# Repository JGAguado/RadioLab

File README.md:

[![GitHub Release][releases-shield]][releases]
[![License][license-shield]](LICENSE)

[![Project Maintenance][maintenance-shield]][maintenance]
[![BuyMeCoffee][buymecoffee-shield]][buymecoffee]

# RadioLab
The RadioLab board is an electronic board intended for transmitting wireless signal values in the most easy and transparent way for the user.

## Project tree

<li><a href="./Design/">Design</a></li>
<li><a href="./Documentation/">Documentation</a></li>

<li><a href="./README.md">README.md</a></li>

[releases-shield]: https://img.shields.io/github/release/JGAguado/RadioLab.svg?style=for-the-badge
[releases]: https://github.com/JGAguado/RadioLab/releases

[license-shield]: https://img.shields.io/badge/License-CC%20BY--NC--SA%204.0-lightgrey.svg?style=for-the-badge

[maintenance-shield]: https://img.shields.io/badge/maintainer-J.%20G.%20Aguado-blue.svg?style=for-the-badge
[maintenance]: https://github.com/JGAguado

[buymecoffee-shield]: https://img.shields.io/badge/buy%20me%20a%20coffee-support-yellow.svg?style=for-the-badge
[buymecoffee]: https://www.buymeacoffee.com/J.G.Aguado

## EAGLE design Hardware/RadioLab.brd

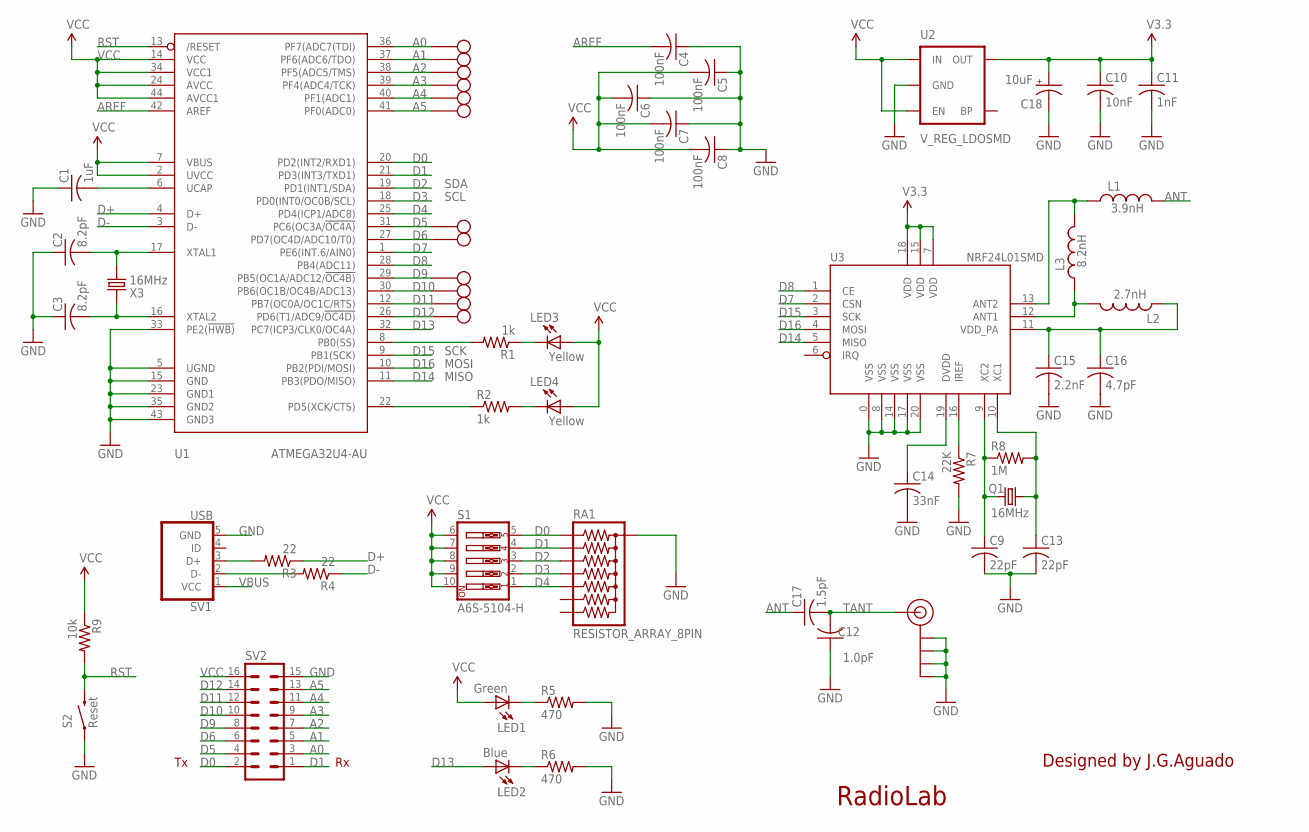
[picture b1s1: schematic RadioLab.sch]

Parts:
ANT: SMA_EDGE; SMA-EDGE
C1: 1uF; C0402
C2, C3: 8.2pF; C0402
C4, C5, C6, C7, C8: 100nF; C0402
C9, C13: 22pF; C0402
C10: 10nF; C0402
C11: 1nF; C0402
C12: 1.0pF; C0402
C14: 33nF; C0402
C15: 2.2nF; C0402
C16: 4.7pF; C0402
C17: 1.5pF; C0402
C18: 10uF; EIA3216
L1: 3.9nH; C0402
L2: 2.7nH; C0402
L3: 8.2nH; C0402
LED1: Green; SML0603
LED2: Blue; SML0603
LED3, LED4: Yellow; SML0603
Q1: 16MHz; CRYSTAL-SMD-5X3
R1, R2: 1k; R0402
R3, R4: 22; R0402
R5, R6: 470; R0402
R7: 22K; R0402
R8: 1M; R0402
R9: 10k; R0402
RA1: RESISTOR_ARRAY_8PIN; CRA12E
S1: A6S-5104-H
S2: Reset; TACTILE_SWITCH_TALL
SV1: USB; FCI-10103594-0001LF
SV2: MA08-2
U1: ATMEGA32U4-AU; TQFP44
U2: V_REG_LDOSMD; SOT23-5
U3: NRF24L01SMD; QFN20
U$1, U$2, U$3, U$4, U$5, U$6, U$7, U$8, U$9, U$10, U$11, U$12: PIN_PAD_CIRCLE_R50; PAD_5MM
X3: 16MHz; 2P-SMD-5X3.2

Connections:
3.3V: C10.1, C11.1, C18.A (+), U2.5 (OUT), U3.7 (VDD), U3.15 (VDD), U3.18 (VDD)
A0: SV2.3, U1.36 (PF7(ADC7(TDI)), U$1.PAD
A1: SV2.5, U1.37 (PF6(ADC6/TDO)), U$2.PAD
A2: SV2.7, U1.38 (PF5(ADC5/TMS)), U$3.PAD
A3: SV2.9, U1.39 (PF4(ADC4/TCK)), U$4.PAD
A4: SV2.11, U1.40 (PF1(ADC1)), U$5.PAD
A5: SV2.13, U1.41 (PF0(ADC0)), U$6.PAD
ANT: C17.1, L1.2
AREF: C4.2, U1.42 (AREF)
D0: RA1.1, S1.5, SV2.2, U1.20 (PD2(INT2/RXD1))
D1: RA1.2, S1.4, SV2.1, U1.21 (PD3(INT3/TXD1))
D2: RA1.3, S1.3, U1.19 (PD1(INT1/SDA))
D3: RA1.4, S1.2, U1.18 (PD0(INT0/OC0B/SCL))
D4: RA1.5, S1.1, U1.25 (PD4(ICP1/ADC8))
D5: SV2.4, U1.31 (PC6(OC3A/!OC4A)), U$7.PAD
D6: SV2.6, U1.27 (PD7(OC4D/ADC10/T0)), U$8.PAD
D7: U1.1 (PE6(INT.6/AIN0)), U3.2 (CSN)
D8: U1.28 (PB4(ADC11)), U3.1 (CE)
D9: SV2.8, U1.29 (PB5(OC1A/ADC12/!OC4B)), U$9.PAD
D10: SV2.10, U1.30 (PB6(OC1B/OC4B/ADC13)), U$10.PAD
D11: SV2.12, U1.12 (PB7(OC0A/OC1C/RTS)), U$11.PAD
D12: SV2.14, U1.26 (PD6(T1/ADC9/!OC4D)), U$12.PAD
D13: LED2.A, U1.32 (PC7(ICP3/CLK0/OC4A))
D14: U1.11 (PB3(PDO/MISO)), U3.5 (MISO)
D15: U1.9 (PB1(SCK)), U3.3 (SCK)
D16: U1.10 (PB2(PDI/MOSI)), U3.4 (MOSI)
D17/PB0/RXLED1: R1.2, U1.8 (PB0(SS))
D+: R3.1, U1.4 (D+)
D-: R4.1, U1.3 (D-)
GND: ANT.GND@0 (GND), ANT.GND@1 (GND), ANT.GND@2 (GND), ANT.GND@3 (GND), C1.1, C2.1, C3.1, C4.1, C5.1, C6.1, C7.1, C8.1, C9.2, C10.2, C11.2, C12.1, C13.2, C14.2, C15.2, C16.2, C18.C (-), R5.2, R6.2, R7.2, RA1.8, S2.A2 (1), SV1.5 (GND), SV2.15, U1.5 (UGND), U1.15 (GND), U1.23 (GND1), U1.33 (PE2(!HWB)), U1.35 (GND2), U1.43 (GND3), U2.2 (GND), U3.0 (VSS), U3.8 (VSS), U3.14 (VSS), U3.17 (VSS), U3.20 (VSS)
unnamed: C9.1, Q1.1, R8.1, U3.9 (XC2)
unnamed: R3.2, SV1.3 (D+)
unnamed: C2.2, U1.17 (XTAL1), X3.2
unnamed: R4.2, SV1.2 (D-)
unnamed: C13.1, Q1.3 (2), R8.2, U3.10 (XC1)
unnamed: LED1.C, R5.1
unnamed: C3.2, U1.16 (XTAL2), X3.1
unnamed: L1.1, L3.2, U3.13 (ANT2)
unnamed: LED2.C, R6.1
unnamed: C15.1, C16.1, L2.1, U3.11 (VDD_PA)
unnamed: R7.1, U3.16 (IREF)
unnamed: C14.1, U3.19 (DVDD)
unnamed: L2.2, L3.1, U3.12 (ANT1)
unnamed: LED4.C, R2.2
unnamed: LED3.C, R1.1
PD5/TXLED1: R2.1, U1.22 (PD5(XCK/CTS))
RST: R9.2, S2.B2 (2), U1.13 (/RESET)
TANT: ANT.SIG (SIGNAL), C12.2, C17.2
UCAP1: C1.2, U1.6 (UCAP)
VBUS: SV1.1 (VCC)
VCC: C5.2, C6.2, C7.2, C8.2, LED1.A, LED3.A, LED4.A, R9.1, S1.6, S1.7, S1.8, S1.9, S1.10, SV2.16, U1.2 (UVCC), U1.7 (VBUS), U1.14 (VCC), U1.24 (AVCC), U1.34 (VCC1), U1.44 (AVCC1), U2.1 (IN), U2.3 (EN)

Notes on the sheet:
RadioLab
Designed by J.G.Aguado
SCK
MOSI
MISO
SDA
SCL

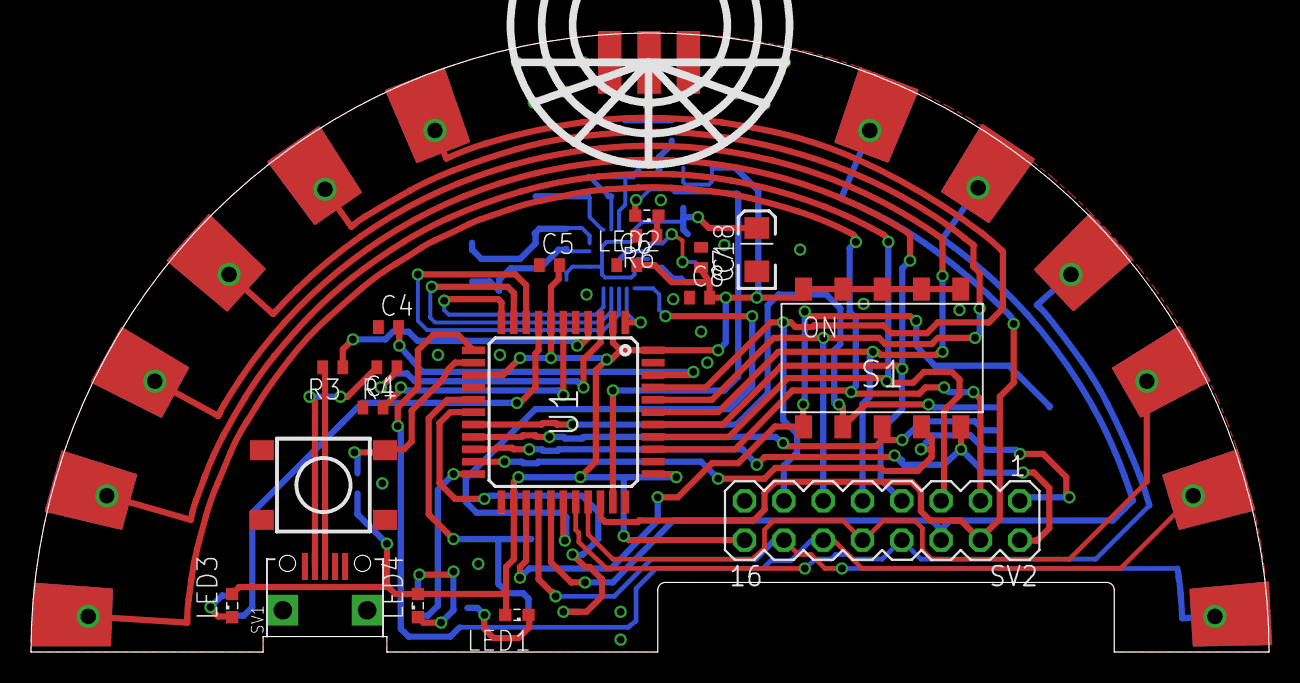
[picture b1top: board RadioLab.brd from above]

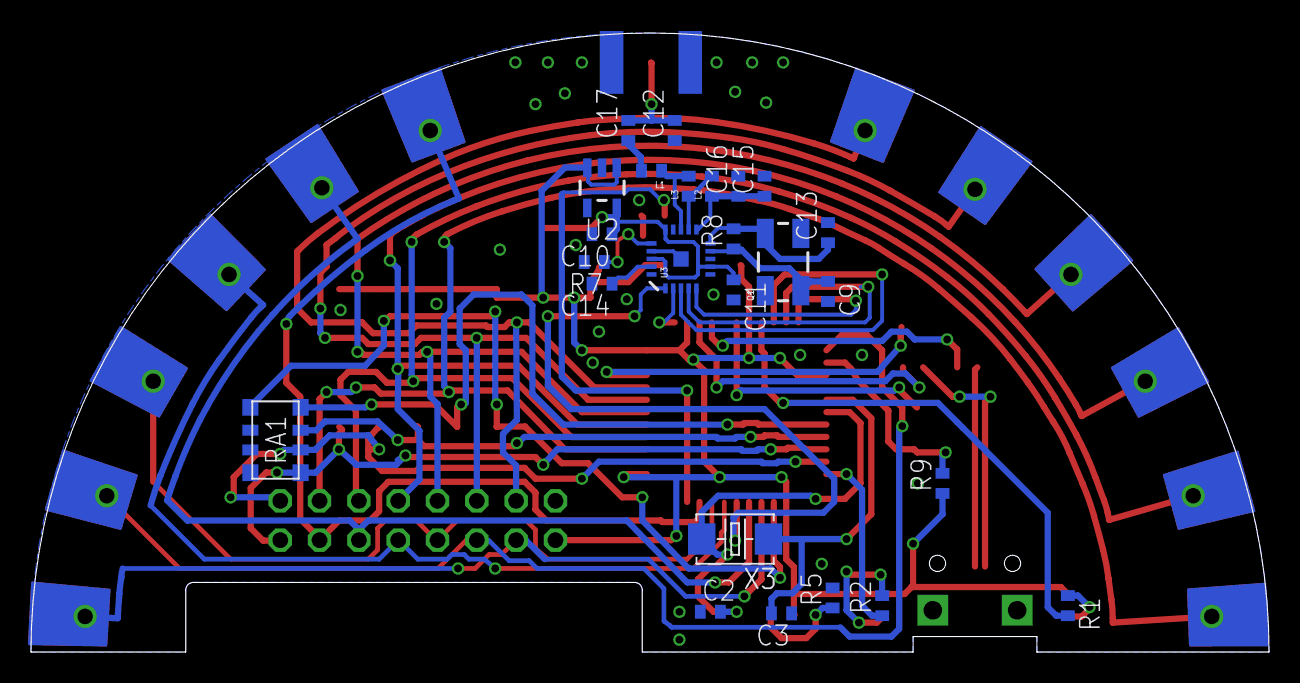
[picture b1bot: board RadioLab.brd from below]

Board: 2 copper layers, 80.0 x 40.0 mm, 57 parts (25 on the bottom side), 50 nets.

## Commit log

2018-01-09 First commit: -Schematic -Board: ~80% routed
2018-02-04 Added Production Files
2018-02-04 Updated SCH and BRD
2018-02-09 Global updates
2022-04-15 Updated structure
